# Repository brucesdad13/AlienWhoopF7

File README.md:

# AlienWhoopF7 Features :alien:
AlienWhoop flight controller for Tiny Whoop, Blade Inductrix, Eachine, BetaFPV, and other micro brushed quadcopter frames. Best in class flight controller running BetaFlight or Butterflight--surface mount soldering required.

* Choice of the top performing ARM processors: 
  * High-performance ST Microelectronics ARM Cortex-M4 core F4 168 MHz CPU
  * High-performance ST Microelectronics ARM Cortex-M7 core F7 216 MHz CPU
* Choice of top performing motion processors: 
  * Invensense MPU-6500 Six-Axis (Gyro + Accelerometer) low power consumption MEMS MotionTracking™ Device
  * Invensense MPU-9250 Nine-Axis (Gyro + Accelerometer + Compass) low power consumption MEMS MotionTracking™ Device
* Latest BetaFlight firmware running the ALIENWHOOPF4 target
* Butterflight firmware supported (iNav under final testing)
* Overkill power MOSFETs capable of extreme brushed motor insanity (6mm, 7mm, 8mm, 8.5mm, and 10mm coreless scream)
* Multiple UARTs for receivers and other devices (e.g. LED strip, beeper)
* Dedicated UART with inverter for FrSky and Futaba SBUS
* UART pads on top conveniently located for SmartAudio VTX control
* Blackbox logging via onboard dataflash chip
* Note: pilots must supply external receiver. Officially supporting FrSky XM, XM+, R-XSR (SBUS,F.PORT), LemonRX DSM2 and DSMX (SBUS), and FlySky FS-A8S (iBUS) satellites.
* 0.8mm 2oz Copper ENIG (gold) finish purple PCBs from OSH Park recommended

## DIY Flight Controller :alien:
If you fancy doing it yourself (DIY), and have the right equipment and patience, building an AlienWhoop from scratch can be tremendously satisfying--though not for the faint of heart. After doing your homework the first step is to place an order for blank PCBs from [OSH Park](https://oshpark.com/shared_projects/p4hs6DbI):
* We recommend ordering the 2oz copper 0.8mm thickness PCB
  * *It takes about three weeks to make the thin boards which allows plenty of time to order components from the bill of materials in the resources folder.*
  * **Please note there are slight changes to the bill of materials (BOM) depending which MCU you choose (F4 vs F7). These MCUs are not 100% pin compatible.**
   * F4: components C7 and C10 place 4.7uF ceramic capacitors and C15 substitute 0 ohm resistor (0R).
   * F7: components C7, C10, and C15 place 4.7uF ceramic capacitor.

## Official AlienWhoop pages :alien:
AlienWhoop has many ways for you to stay engaged. Please Like and/or Follow Us for regular updates in your status feed related to AlienWhoop, DIY electronics, and micro brushed quadcopter related posts.
* http://fb.me/alienwhoop/ Facebook
* http://alienwhoop.us/ News and products
* http://alienwhoop.us/git-config CLI diff files for Betaflight and Butterflight
* http://alienwhoop.us/discord Join our Discord chat and hang out with the community or ask questions

## See the AlienWhoop in action on YouTube :alien:

May this work be of benefit and bring much joy and happiness!

## Acknowledgements :alien:

AlienWhoop V2.1 Dev Team:
* Charles Stevenson (brucesdad13)
* Travis Schrock (NotFastEnuf)
* Brian Pichardo (VelcroFPV)
* Michael Montiverdi (MontiFPV)

Deep bows of appreciation and thanks to Lance for his original work and tremendous
generosity in releasing his labor of love for the benefit of all flight controller
enthusiasts. Check out AlienWhoop's ancestry in our preserved copy of Lance's original AlienFlight
github repository of open source hardware flight controllers: the [Classic FC aka Classic Narrow](https://github.com/brucesdad13/AlienFlightArchive/blob/master/Flight-Controllers/Classic#narrow-classic-flight-controller), [F3 Quad FC](https://github.com/brucesdad13/AlienFlightArchive/blob/master/Flight-Controllers/F3-V1/F3-Quad#f3-quad-brushed-v1-flight-controller), [F3 Hexa FC](https://github.com/brucesdad13/AlienFlightArchive/blob/master/Flight-Controllers/F3-V1/F3-Hexa#f3-hexa-brushed-v1-flight-controller), and [F3 Octo FC](https://github.com/brucesdad13/AlienFlightArchive/blob/master/Flight-Controllers/F3-V1/F3-Octo#f3-octo-brushed-v1-flight-controller).
*As of late July 2017, the original www.alienflight.com site is no longer in operation.

Equally deep bows to Jesse Perkins, creator of Tiny Whoop, and the source of inspiration and love for tiny brushed quads.
* http://www.tinywhoop.com/ ~
* https://www.facebook.com/groups/tinywhoop/ ~

~ Please note: **AlienWhoop** is not affiliated with nor endorsed by AlienFlight or forks of Lance's work such as AlienFlight NG. The use of Alien in the name and the alien head vector graphic used on the board silkscreen are nods to the lineage of this remix and to the work of Lance and others who created the conditions for this project to arise. Likewise, AlienWhoop is not affiliated with nor endorsed by Tiny Whoop. The Whoop in the name comes from Jesse Perkin's fantastic Tiny Whoop ("a small first-person-view aircraft that truly allows you to feel the gift of flight and the feeling of being tiny" [tinywhoop.com]) and is simply a nod to his efforts and the TW community worldwide.

## If you like this project and want to support further development
* https://paypal.me/AlienWhoop/ 
* http://shop.alienwhoop.us/ for t-shirts and gear

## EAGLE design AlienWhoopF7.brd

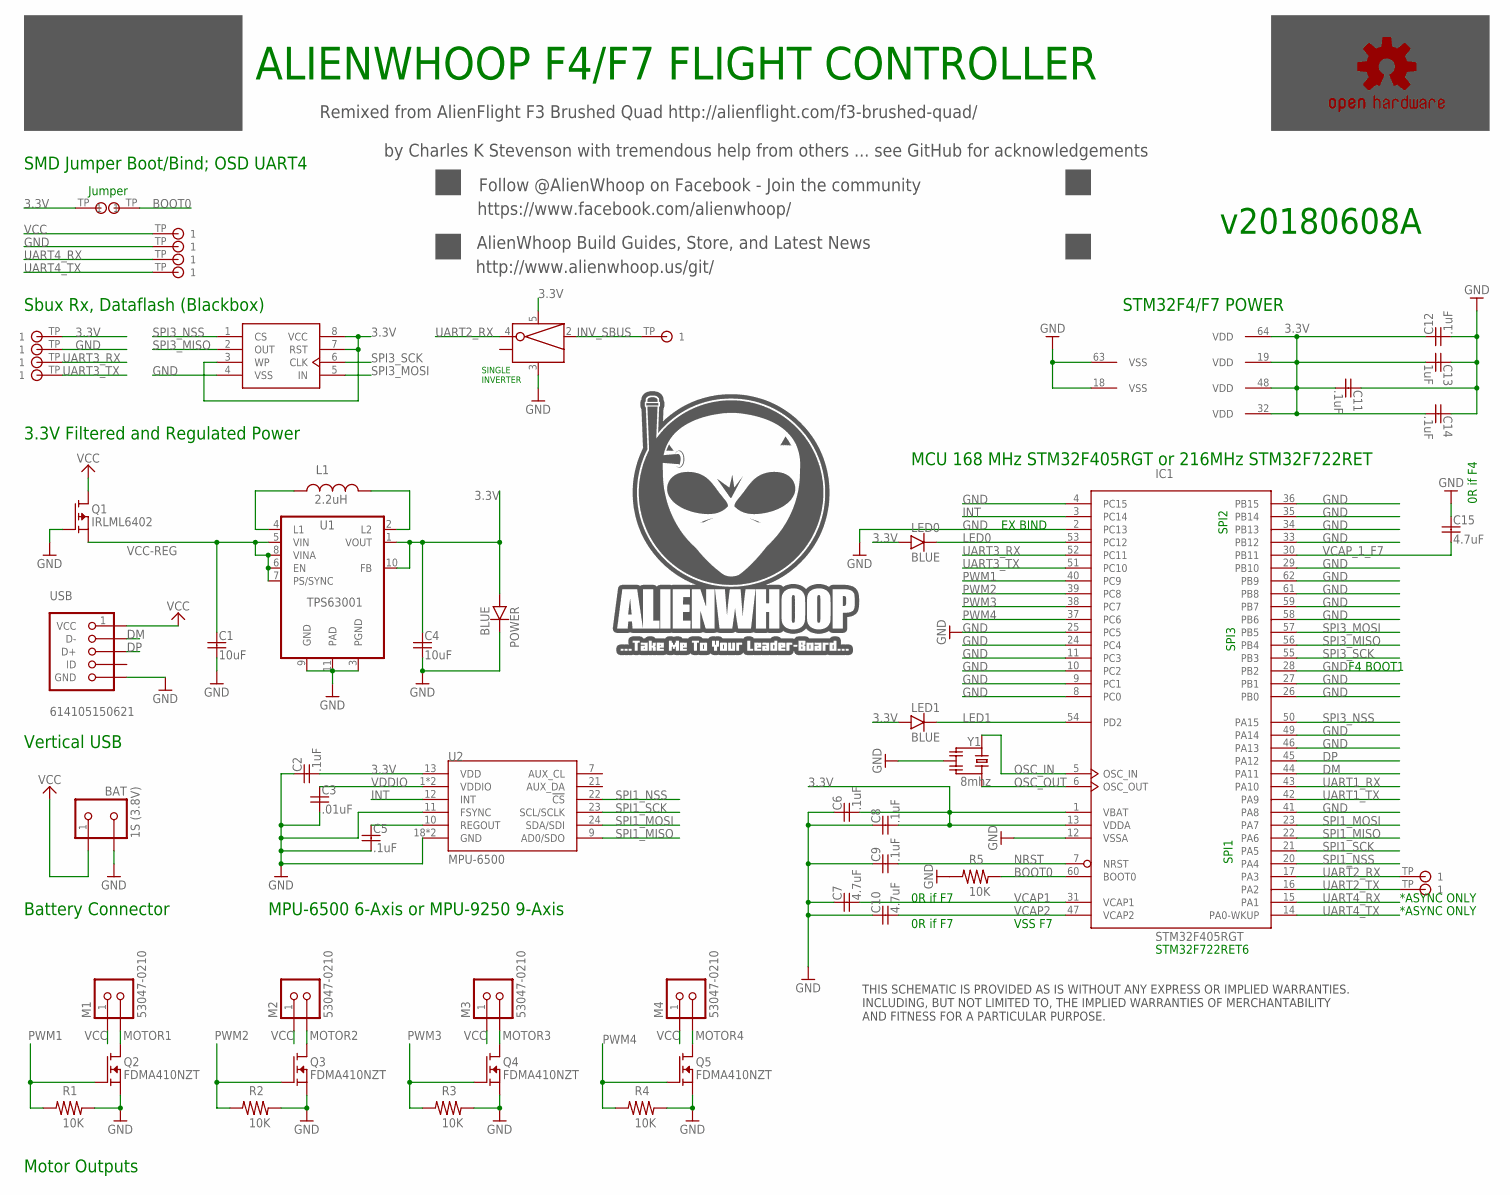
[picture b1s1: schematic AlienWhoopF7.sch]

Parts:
3.3V, 3V3: TESTPAD; PARTNO TESTPAD
BAT: 1S (3.8V); S2B-PH-K-S
BOOT: TESTPAD; PARTNO TESTPAD
C1, C4: 10uF; YUDEN-CAP-0805
C2, C5, C6, C8, C9, C11, C12, C14: .1uF; MUR-CAP-0603
C3: .01uF; MUR-CAP-0603
C7, C10, C15: 4.7uF; MUR-CAP-0603
C13: 1uF; MUR-CAP-0603
GND: TESTPAD; PARTNO TESTPAD
GND@1: TESTPAD; PARTNO TESTPAD
IC1: STM32F405RGT; LQFP64; MPN STM32F045RGT
L1: 2.2uH; DFE201612E-2R2M-P2; PARTNO DFE201612E-2R2M-P2
LED0, LED1: BLUE; SMD-CHIP-LED-0805
LOGO3: OSHW-LOGOS; OSHW-LOGO-S; PARTNO OSHW-LOGOS
M1, M2, M3, M4: 53047-0210; PICO-53047-02
POWER: BLUE; SMD-CHIP-LED-0805
Q1: IRLML6402; SOT-23
Q2, Q3, Q4, Q5: FDMA410NZT; MICROFET-2X2; PARTNO FDMA410NZT
R1, R2, R3, R4, R5: 10K; VISH-RES-0603
RX2, RX2/INV, RX3, RX4: TESTPAD; PARTNO TESTPAD
TX2, TX3, TX4: TESTPAD; PARTNO TESTPAD
U1: TPS63001; VSON-N10
U2: MPU-6500; QFN24_PAD; PARTNO MPU-6500
U3: MX25L6406EM2I-12G; M25P32; PARTNO MX25L6406EM2I-12G
U4: SN74LVC1G04DBVR; SOT23-5; PARTNO SN74LVC1G04DBVR
USB: 614105150621; USB-BFPV; PARTNO 614105150621
VCC@1: TESTPAD; PARTNO TESTPAD
Y1: 8mhz; RESONATOR_8

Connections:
3.3V: 3.3V.TP, 3V3.TP, C2.2, C4.1, C6.2, C8.2, C11.2, C12.1, C13.2, C14.2, IC1.1 (VBAT), IC1.13 (VDDA), IC1.19 (VDD), IC1.32 (VDD), IC1.48 (VDD), IC1.64 (VDD), LED0.A, LED1.A, POWER.A, U1.1 (VOUT), U1.10 (FB), U2.13 (VDD), U3.3 (WP), U3.7 (RST), U3.8 (VCC), U4.5 (VCC)
BOOT0: BOOT.TP, IC1.60 (BOOT0), R5.1
DM: IC1.44 (PA11), USB.2 (D-)
DP: IC1.45 (PA12), USB.3 (D+)
GND: BAT.2, C1.2, C2.1, C3.2, C4.2, C5.2, C6.1, C7.1, C8.1, C9.1, C10.1, C11.1, C12.2, C13.1, C14.1, C15.1, GND.TP, GND@1.TP, IC1.2 (PC13), IC1.4 (PC15), IC1.8 (PC0), IC1.9 (PC1), IC1.10 (PC2), IC1.11 (PC3), IC1.12 (VSSA), IC1.18 (VSS), IC1.24 (PC4), IC1.25 (PC5), IC1.26 (PB0), IC1.27 (PB1), IC1.28 (PB2), IC1.29 (PB10), IC1.33 (PB12), IC1.34 (PB13), IC1.35 (PB14), IC1.36 (PB15), IC1.41 (PA8), IC1.46 (PA13), IC1.49 (PA14), IC1.58 (PB6), IC1.59 (PB7), IC1.61 (PB8), IC1.62 (PB9), IC1.63 (VSS), POWER.C, Q1.1 (G), Q2.S, Q2.S1 (S), Q3.S, Q3.S1 (S), Q4.S, Q4.S1 (S), Q5.S, Q5.S1 (S), R1.1, R2.1, R3.1, R4.1, R5.2, U1.3 (PGND), U1.9 (GND), U1.11 (PAD), U2.11 (FSYNC), U2.18 (GND), U2.20 (GND), U3.4 (VSS), U4.3 (GND), USB.5 (GND), USB.P$6 (GND), USB.P$7 (GND), Y1.2
INT: IC1.3 (PC14), U2.12 (INT)
INV_SBUS: RX2/INV.TP, U4.2 (A)
L1: L1.P$1 (1), U1.4 (L1)
L2: L1.P$2 (2), U1.2 (L2)
LED0: IC1.53 (PC12), LED0.C
LED1: IC1.54 (PD2), LED1.C
MOTOR1: M1.2, Q2.D, Q2.D1 (D), Q2.D2 (D), Q2.D3 (D), Q2.D4 (D)
MOTOR2: M2.2, Q3.D, Q3.D1 (D), Q3.D2 (D), Q3.D3 (D), Q3.D4 (D)
MOTOR3: M3.2, Q4.D, Q4.D1 (D), Q4.D2 (D), Q4.D3 (D), Q4.D4 (D)
MOTOR4: M4.2, Q5.D, Q5.D1 (D), Q5.D2 (D), Q5.D3 (D), Q5.D4 (D)
NRST: C9.2, IC1.7 (NRST)
OSC_IN: IC1.5 (OSC_IN), Y1.1
OSC_OUT: IC1.6 (OSC_OUT), Y1.3
PWM1: IC1.40 (PC9), Q2.G, R1.2
PWM2: IC1.39 (PC8), Q3.G, R2.2
PWM3: IC1.38 (PC7), Q4.G, R3.2
PWM4: IC1.37 (PC6), Q5.G, R4.2
REGOUT: C5.1, U2.10 (REGOUT)
SPI1_MISO: IC1.22 (PA6), U2.9 (AD0/SDO)
SPI1_MOSI: IC1.23 (PA7), U2.24 (SDA/SDI)
SPI1_NSS: IC1.20 (PA4), U2.22 (!CS)
SPI1_SCK: IC1.21 (PA5), U2.23 (SCL/SCLK)
SPI3_MISO: IC1.56 (PB4), U3.2 (OUT)
SPI3_MOSI: IC1.57 (PB5), U3.5 (IN)
SPI3_NSS: IC1.50 (PA15), U3.1 (CS)
SPI3_SCK: IC1.55 (PB3), U3.6 (CLK)
UART1_RX: IC1.43 (PA10)
UART1_TX: IC1.42 (PA9)
UART2_RX: IC1.17 (PA3), RX2.TP, U4.4 (Y)
UART2_TX: IC1.16 (PA2), TX2.TP
UART3_RX: IC1.52 (PC11), RX3.TP
UART3_TX: IC1.51 (PC10), TX3.TP
UART4_RX: IC1.15 (PA1), RX4.TP
UART4_TX: IC1.14 (PA0-WKUP), TX4.TP
VCAP1: C7.2, IC1.31 (VCAP1)
VCAP2: C10.2, IC1.47 (VCAP2)
VCAP_1_F7: C15.2, IC1.30 (PB11)
VCC: BAT.1, M1.1, M2.1, M3.1, M4.1, Q1.3 (D), USB.1 (VCC), VCC@1.TP
VCC-REG: C1.1, Q1.2 (S), U1.5 (VIN), U1.6 (EN), U1.7 (PS/SYNC), U1.8 (VINA)
VDDIO: C3.1, U2.1 (VDDIO), U2.8 (VDDIO)

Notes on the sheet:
THIS SCHEMATIC IS PROVIDED AS IS WITHOUT ANY EXPRESS OR IMPLIED WARRANTIES. INCLUDING, BUT NOT LIMITED TO, THE IMPLIED WARRANTIES OF MERCHANTABILITY AND FITNESS FOR A PARTICULAR PURPOSE.
Remixed from AlienFlight F3 Brushed Quad http://alienflight.com/f3-brushed-quad/
STM32F4/F7 POWER
MPU-6500 6-Axis or MPU-9250 9-Axis
Motor Outputs
VSS F7
0R if F7
0R if F4
Battery Connector
ALIENWHOOP F4/F7 FLIGHT CONTROLLER
Vertical USB
Sbux Rx, Dataflash (Blackbox)
3.3V Filtered and Regulated Power
STM32F722RET6
SMD Jumper Boot/Bind; OSD UART4
https://www.facebook.com/alienwhoop/
Follow @AlienWhoop on Facebook - Join the community
MCU 168 MHz STM32F405RGT or 216MHz STM32F722RET
by Charles K Stevenson with tremendous help from others ... see GitHub for acknowledgements
v20180608A
SPI1
SPI2
SPI3
*ASYNC ONLY
http://www.alienwhoop.us/git/
AlienWhoop Build Guides, Store, and Latest News
EX BIND
F4 BOOT1
Jumper

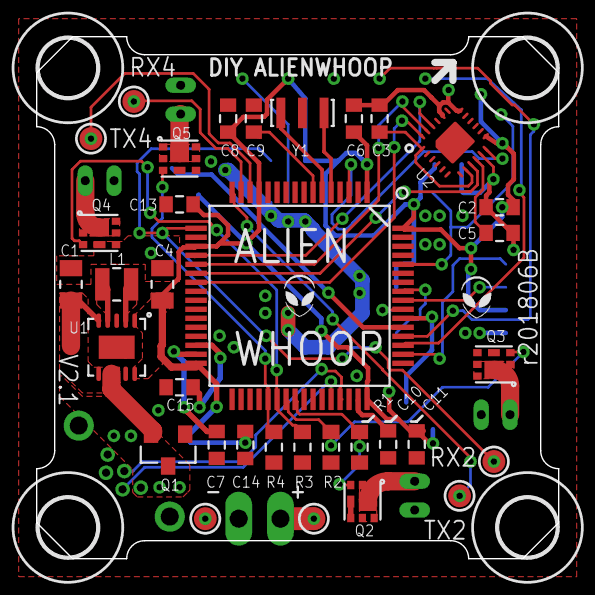
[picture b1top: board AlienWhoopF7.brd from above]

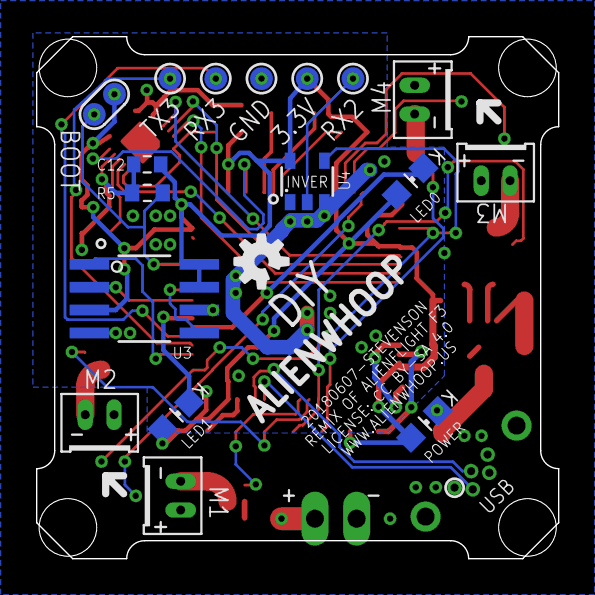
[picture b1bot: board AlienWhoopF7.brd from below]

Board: 2 copper layers, 29.0 x 29.0 mm, 59 parts (21 on the bottom side), 43 nets.

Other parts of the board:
U$1, U$2, U$3, U$4: 3,2

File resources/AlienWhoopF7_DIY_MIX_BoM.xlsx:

Value | Device | Package | Parts/Silkscreen Label | Description | MF | MPN
.01uF | Capacitor 0.01 uF | 0603 | C3 | CAPACITOR | Murata | GRM188R71C103KA01D
.1uF | Capacitor 0.10 uF | 0603 | C2, C5, C6, C8, C9, C11, C12, C14 | CAPACITOR | Murata | GRM188R71C104KA01D
10uF | Capacitor 10.0 uF | 0805 | C1, C4 | CAPACITOR | Taiyo Yuden | JMK212AB7106KG-T
1uF | Capacitor 1.00 uF | 0603 | C13 | CAPACITOR | Murata | GRM188R71C105KA12D
4.7uF | Capacitor 4.70 uF | 0603 | C7, C10 | CAPACITOR | Murata | GRJ188C70J475KE11D
4.7uF | Capacitor 4.70 uF | 0603 | C15 | CAPACITOR | Murata | GRJ188C70J475KE11D
FDMA410NZ | MOSFET | UMLP-6 | Q2, Q3, Q4, Q5 | MOSFET 20V Single N-Ch 1.5V (9.5 amp continuous, 23 amp pulsed) | Fairchild | FDMA410NZ
1S (3.8V) | Connector JST PH 2.0 | S2B-PH-K-S | BAT | 1S LIPO connector to make PowerWhoop 2.0 pigtail w/24AWG wire and heatshrink | JST | S2B-PH-K-S
SBUS | Connector 3-pin Receiver | S3B-ZR | RX | 3 Pin Receiver (optional.. Used if not directly soldering satellite rx to throu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 | JST | S3B-ZR
105133-0011 | Vertical USB Port | 1051330011-SD | USB | Molex USB Connectors uUSB B Rec Vertical TH 2.30 | MOLEX | 105133-0011
IRLML6402 | MOSFET-P | SOT-23 | Q1 | P-Channel MOSFET | IR | IRLML6402
MPU-6500 | MPU-6500 Gyro/Acc | QFN24_PAD | U2 | Invensense MPU-6500 6-axis motion processor gyro accelerometer NO COMPASS | INVENSENSE | MPU-6500
MPU-9250 | MPU-9250 Gyro/Acc/Mag | QFN24_PAD | U2 | Invensense MPU-9250 9-axis motion processor gyro accelerometer compass | INVENSENSE | MPU-9250
2.2uH | Inductor 2.2 uH | TFM201610ALMA | L1 | Thin Film Metal Inductor substituted for Taiyo Yuden | Taiyo Yuden | TFM201610ALMA2R2MTAA
53047-0210 | Connector Brushed Motor | PICO-53047-02 | M1, M2, M3, M4 | Motor Connector | MOLEX | 53047-0210
0R | Resistor 0.00 Ohms | 0603 | C15 | RESISTOR used as Jumper | Yageo | RC0603FR-070RL
0R | Resistor 0.00 Ohms | 0603 | C7, C10 | RESISTOR used as Jumper | Yageo | RC0603FR-070RL
10K | Resistor 10K Ohms | 0603 | R1, R2, R3, R4, R5 | RESISTOR | Vishay | CRCW060310K0FKEAHP
8mhz | Resonator 8 MHz | RESONATOR_8 | Y1 | SMD Ceramic Resonators | Murata | CSTCE8M00G55-R0
BLUE | LED (blue as spec'd only!) | 0805 | LED0, LED1, PWR | SMD CHIP LED | Kingbright | APHCM2012QBC/D-F01
STM32F4/F7 | STM32F405RGT | LQFP64 | IC1 | ARM 32-bit Cortex™-M3 168 MHz CPU |  | STM32F405RGT6
STM32F4/F7 | STM32F722RET | LQFP64 | IC1 | ARM 32-bit Cortex™-M4 216 MHz CPU |  | STM32F722RET6
TPS63001 | TPS630XX-TPS63001 | VSON-N10 | U1 | Buck/Boost Converter | TI | TPS63001DRCR
AW-F4-BR-V2-PCB | AW-F4-BR-V2-PCB | PCB | PCB | PCB 0.8mm thick 2oz copper | OSH Park | AlienWhoop F7 DIY MIX
* Yellow highlighted rows are for F4 builds or in case of MPU-9250 optional upg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
** LED circuits lack current limiting resistor so only specified blue LED can b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

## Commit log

2017-08-11 Initial import of AlienWhoop F7 DIY MIX (backwards compatible to F4 processor). Graciously remixed from Lance's AlienFlight F3 Brushed Quad FC. Compatible with BetaFlight 3.2 RC1 and beyond. License: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
2017-08-11 Set theme jekyll-theme-architect
2018-06-08 Updated to V2.1 with Blackbox
2018-06-08 Updated to match V2.1 dev team and notes

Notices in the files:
AlienWhoopF7.brd:
Released under the Creative Commons Attribution-ShareAlike 4.0 International License
https://creativecommons.org/licenses/by-sa/4.0
LICENSE: CC BY-SA 4.0
parts and their libraries:
SparkFun-Aesthetics: Licensing: Creative Commons ShareAlike 4.0 International - https://creativecommons.org/licenses/by-sa/4.0
alienflight: License: CC BY SA
alienflight: Released under the Creative Commons
Attribution Share-Alike 4.0 License
http://creativecommons.org/licenses/by-sa/4.0
